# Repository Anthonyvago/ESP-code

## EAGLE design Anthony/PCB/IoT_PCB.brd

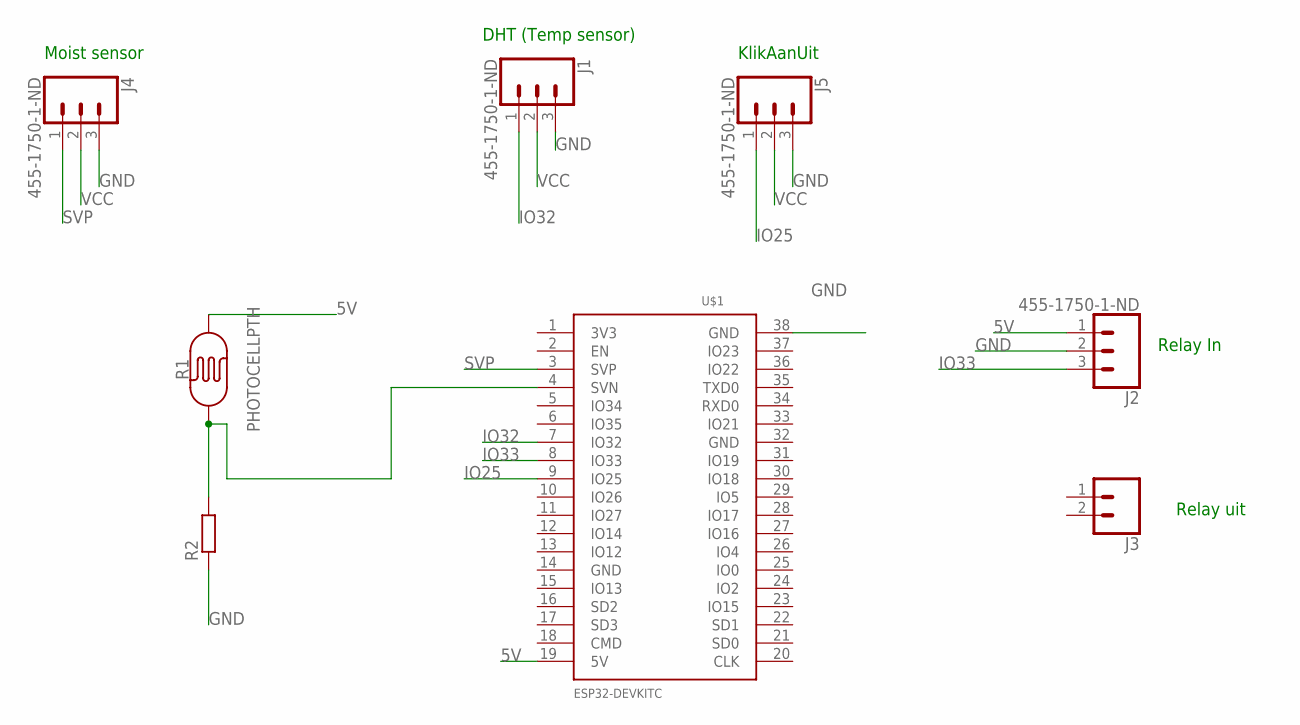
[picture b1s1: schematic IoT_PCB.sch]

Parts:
J1, J2, J4, J5: 455-1750-1-ND; 1X03
J3: CONN_02; 1X02
R1: PHOTOCELLPTH; PHOTOCELL
R2: R-EU_0207/10; 0207/10
U$1: ESP32DEVKITC; ESP32-DEVKITC

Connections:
5V: J2.1, R1.2, U$1.19 (5V)
GND: J1.3, J2.2, J4.3, J5.3, R2.1, U$1.38 (GND)
IO25: J5.1, U$1.9 (IO25)
IO32: J1.1, U$1.7 (IO32)
IO33: J2.3, U$1.8 (IO33)
unnamed: R1.1, R2.2, U$1.4 (SVN)
SVP: J4.1, U$1.3 (SVP)
VCC: J1.2, J4.2, J5.2

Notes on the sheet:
DHT (Temp sensor)
Moist sensor
KlikAanUit
Relay In
Relay uit

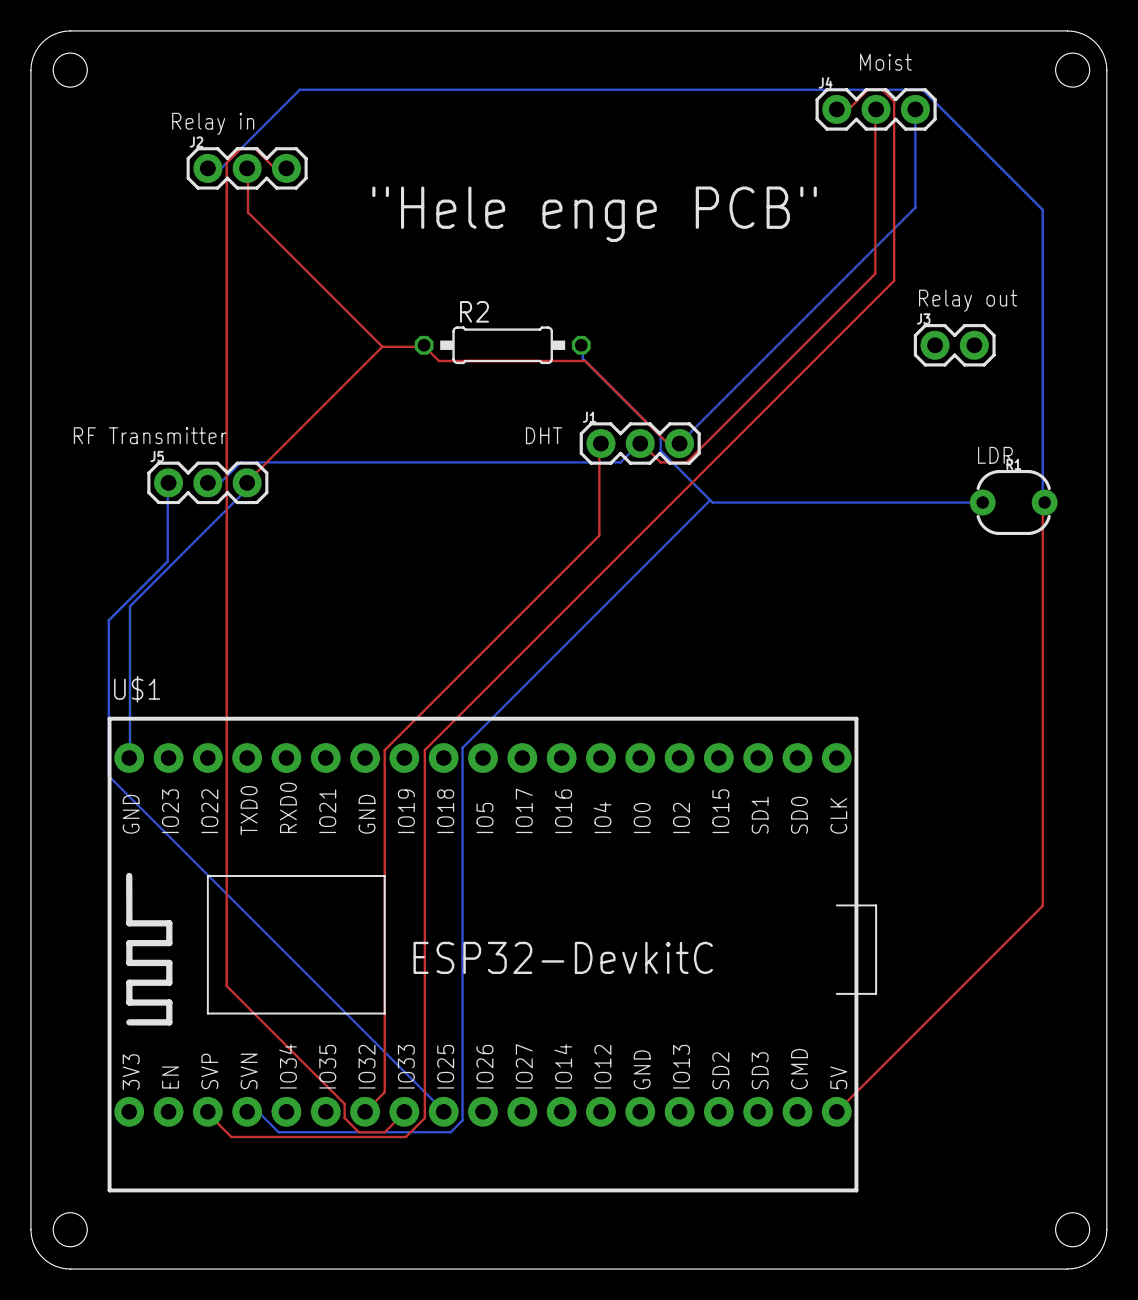
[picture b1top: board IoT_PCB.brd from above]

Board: 2 copper layers, 69.5 x 80.0 mm, 8 parts (0 on the bottom side), 8 nets.

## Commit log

2023-03-02 replace
2023-03-02 baud rate update
2023-03-02 moved dirs
2023-03-02 basic funcs added
2023-03-02 perfectionists be like
2023-03-02 submodule portfolio added
2023-03-02 removed unnecessary file
2023-03-02 added submodule config
2023-03-02 Added 3D model of the cup
2023-03-02 leerkaart added
2023-03-09 bakje update
2023-03-09 alle mogelijke sensorwaardes in de cloud
2023-03-09 3D- printje geupdatet
2023-03-10 Added light sensor
2023-03-10 changed light values
2023-03-14 rename
2023-03-14 removed unnecessary dirs
2023-03-14 doe het nou
2023-03-14 test
2023-03-14 remvoed submodule
2023-03-14 Ädded submodule again
2023-03-17 TOM-model added to learnt list
2023-03-23 edited dir structure
2023-03-23 3d print
2023-04-04 added pcb
2023-04-25 dnekw
2023-04-25 nwediew
2023-05-10 Bakje geüpdatet
2023-05-24 upload van print bestanden

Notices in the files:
parts and their libraries:
SparkFun-Connectors: Licensing: Creative Commons ShareAlike 4.0 International - https://creativecommons.org/licenses/by-sa/4.0
